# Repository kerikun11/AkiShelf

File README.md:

# AkiShelf
Display of Akizuki's Shelf Number

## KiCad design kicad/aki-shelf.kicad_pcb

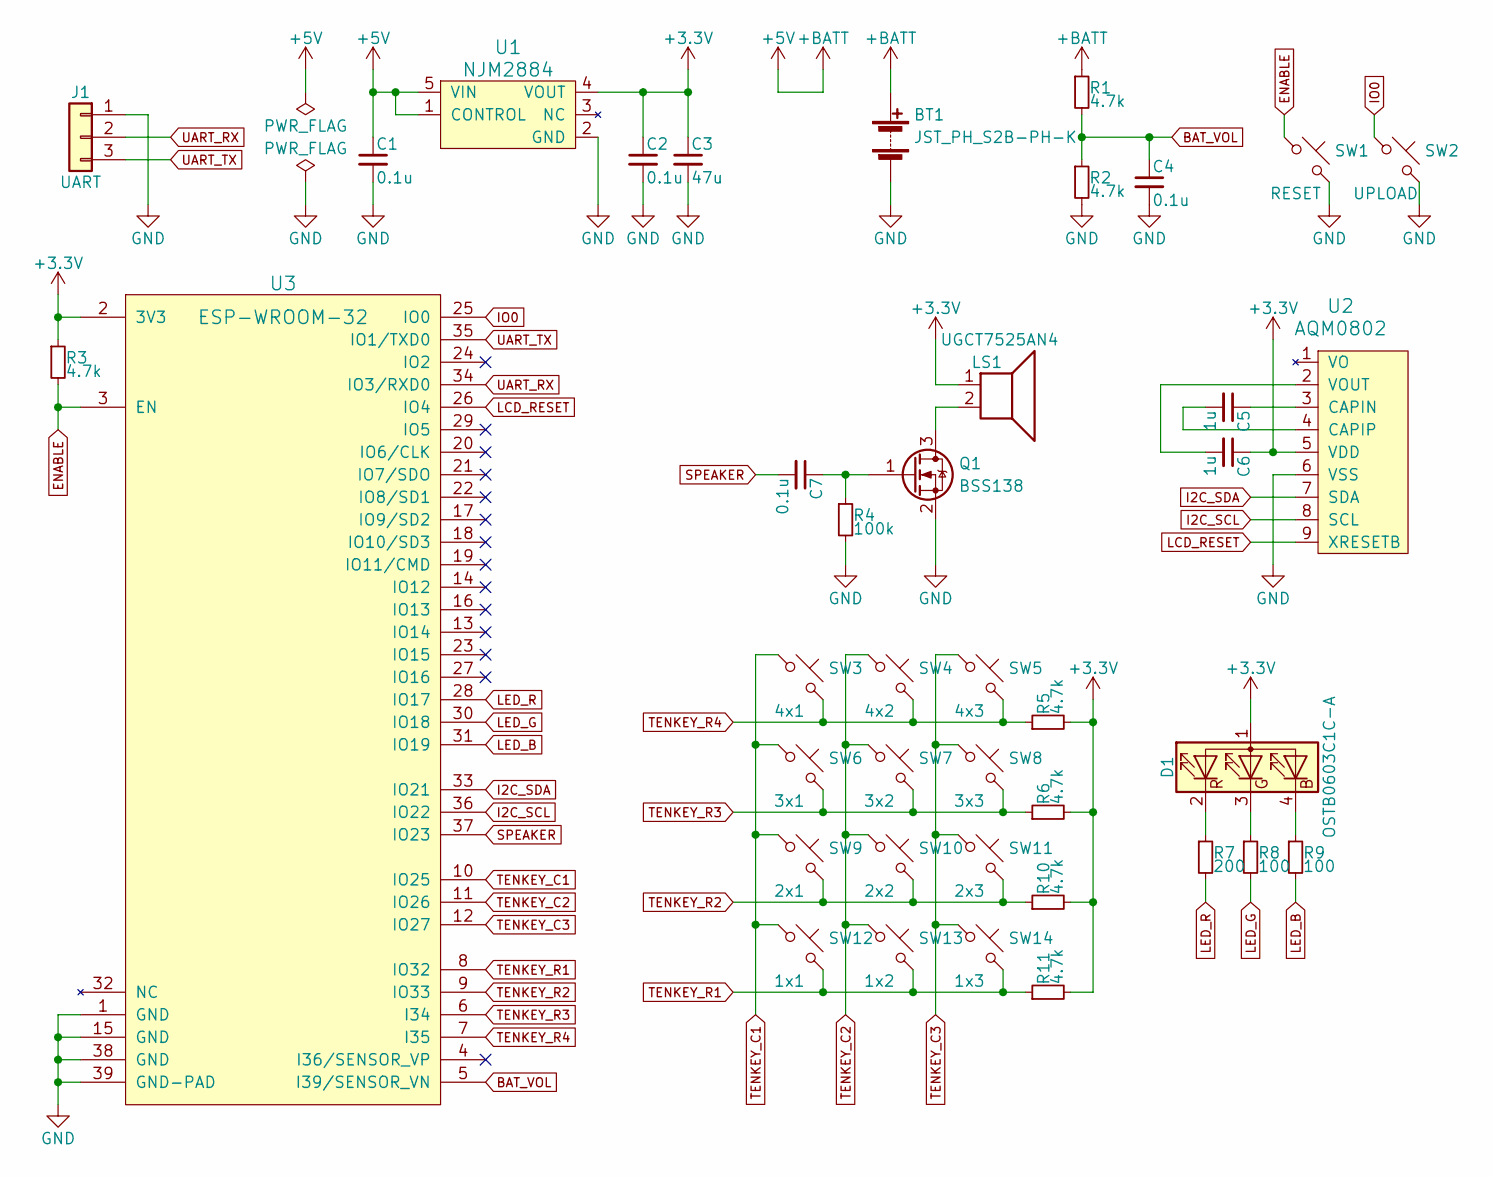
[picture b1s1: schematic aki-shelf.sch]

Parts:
BT1: JST_PH_S2B-PH-K; JST_PH_S2B-PH-K_02x2.00mm_Angled
C1, C2, C4, C7: 0.1u; C_0603
C3: 47u; C_1206
C5, C6: 1u; C_0603
D1: OSTB0603C1C-A
J1: UART; Socket_Strip_Straight_1x03_Pitch2.54mm
LS1: UGCT7525AN4
Q1: BSS138; SOT-23
R1, R2, R3, R5, R6, R10, R11: 4.7k; R_0603
R4: 100k; R_0603
R7: 200; R_0603
R8, R9: 100; R_0603
SW1: RESET; SKRPACE010
SW2: UPLOAD; SKRPACE010
SW3: 4x1; SKRPACE010
SW4: 4x2; SKRPACE010
SW5: 4x3; SKRPACE010
SW6: 3x1; SKRPACE010
SW7: 3x2; SKRPACE010
SW8: 3x3; SKRPACE010
SW9: 2x1; SKRPACE010
SW10: 2x2; SKRPACE010
SW11: 2x3; SKRPACE010
SW12: 1x1; SKRPACE010
SW13: 1x2; SKRPACE010
SW14: 1x3; SKRPACE010
U1: NJM2884; SOT-89-5_Housing
U2: AQM0802; AQM0802A-RN-GBW
U3: ESP-WROOM-32

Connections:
+3V3: C2.1, C3.1, C6.1, D1.1 (A), LS1.1, R3.1, R5.2, R6.2, R10.2, R11.2, U1.4 (VOUT), U2.5 (VDD), U3.2 (3V3)
+5V: BT1.1 (+), C1.1, R1.1, U1.1 (CONTROL), U1.5 (VIN)
BAT_VOL: C4.1, R1.2, R2.1, U3.5 (I39/SENSOR_VN)
ENABLE: R3.2, SW1.1, U3.3 (EN)
GND: BT1.2 (-), C1.2, C2.2, C3.2, C4.2, J1.1, Q1.2 (S), R2.2, R4.2, SW1.2, SW2.2, U1.2 (GND), U2.6 (VSS), U3.1 (GND), U3.15 (GND), U3.38 (GND), U3.39 (GND-PAD)
I2C_SCL: U2.8 (SCL), U3.36 (IO22)
I2C_SDA: U2.7 (SDA), U3.33 (IO21)
IO0: SW2.1, U3.25 (IO0)
LCD_RESET: U2.9 (XRESETB), U3.26 (IO4)
LED_B: R9.2, U3.31 (IO19)
LED_G: R8.2, U3.30 (IO18)
LED_R: R7.2, U3.28 (IO17)
unnamed: C5.1, U2.3 (CAPIN)
unnamed: C5.2, U2.4 (CAPIP)
unnamed: C6.2, U2.2 (VOUT)
unnamed: C7.1, Q1.1 (G), R4.1
unnamed: D1.2 (RK), R7.1
unnamed: D1.3 (GK), R8.1
unnamed: D1.4 (BK), R9.1
unnamed: LS1.2, Q1.3 (D)
SPEAKER: C7.2, U3.37 (IO23)
TENKEY_C1: SW3.1, SW6.1, SW9.1, SW12.1, U3.10 (IO25)
TENKEY_C2: SW4.1, SW7.1, SW10.1, SW13.1, U3.11 (IO26)
TENKEY_C3: SW5.1, SW8.1, SW11.1, SW14.1, U3.12 (IO27)
TENKEY_R1: R11.1, SW12.2, SW13.2, SW14.2, U3.8 (IO32)
TENKEY_R2: R10.1, SW9.2, SW10.2, SW11.2, U3.9 (IO33)
TENKEY_R3: R6.1, SW6.2, SW7.2, SW8.2, U3.6 (I34)
TENKEY_R4: R5.1, SW3.2, SW4.2, SW5.2, U3.7 (I35)
UART_RX: J1.2, U3.34 (IO3/RXD0)
UART_TX: J1.3, U3.35 (IO1/TXD0)

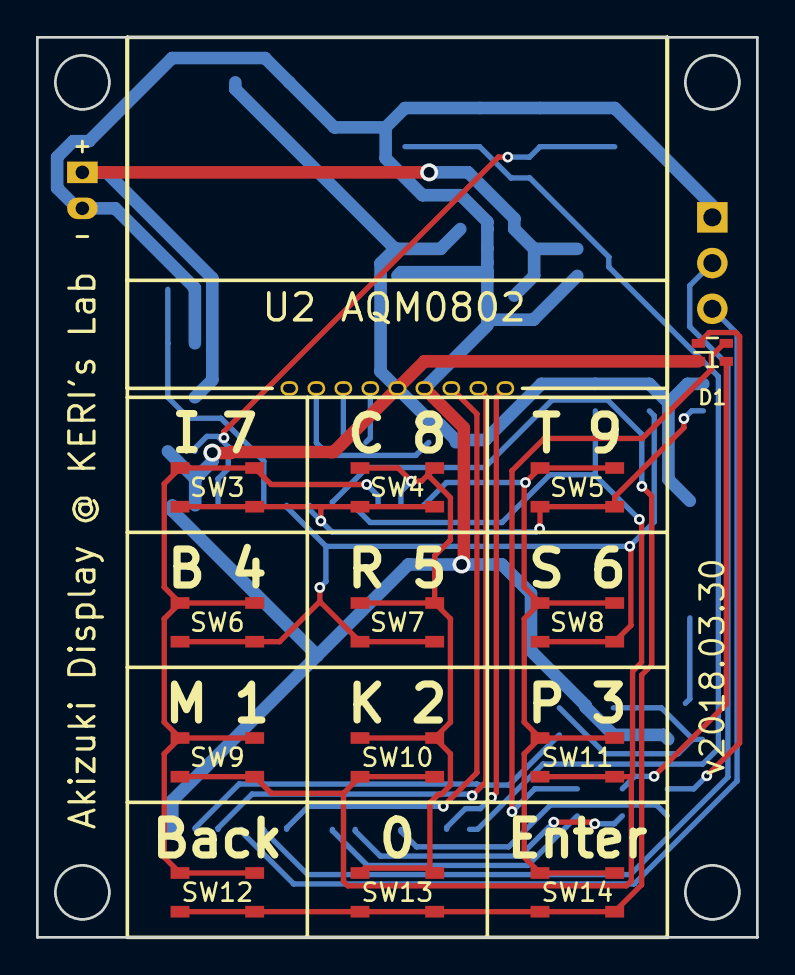
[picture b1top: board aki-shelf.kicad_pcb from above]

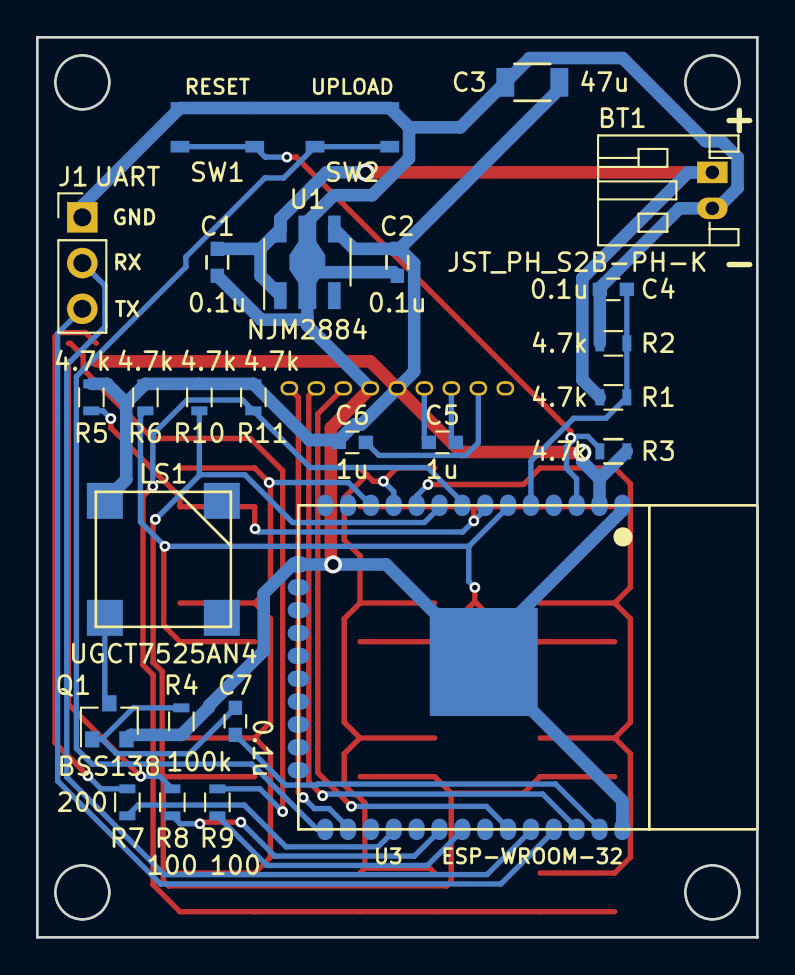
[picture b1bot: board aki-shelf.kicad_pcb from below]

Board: 2 copper layers, 40.0 x 50.0 mm, 40 parts (26 on the bottom side), 30 nets.

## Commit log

2018-02-21 ソースコードを追加
2018-02-21 KiCadファイルを追加
2018-02-22 自動配線を適用
2018-02-22 基板を両面にして小型化
2018-02-24 穴径を3mmに変更
    貼り付けボスが使えるように
2018-02-25 ログ出力を改良
2018-03-10 LEDの点灯コードを追加
2018-04-30 基板を改良
    スイッチの位置，スピーカーの回路など
2023-01-02 リダイレクトのエラーを修正
2023-01-02 platformio.ini を追加
2023-01-02 回路図を追加
2023-01-02 auto sleep
